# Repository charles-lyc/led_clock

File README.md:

# led_clock
led clock, matrix dot, esp32, temp/humidity/weather online and offline.

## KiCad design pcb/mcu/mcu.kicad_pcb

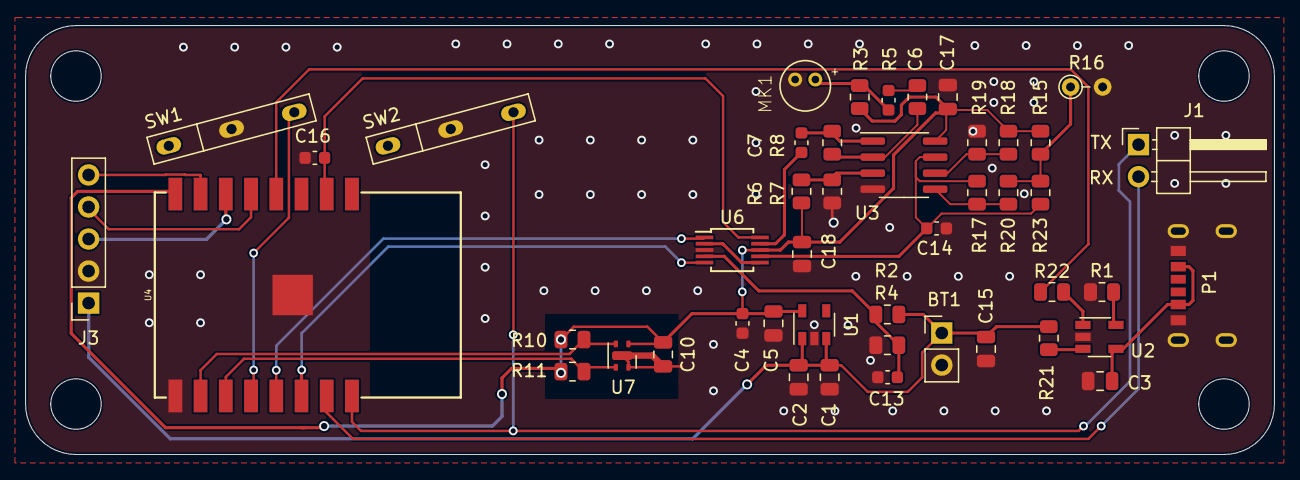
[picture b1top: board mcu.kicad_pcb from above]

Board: 2 copper layers, 99.0 x 34.0 mm, 46 parts (0 on the bottom side), 31 nets.

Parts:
BT1: Battery_Cell; PinHeader_1x02_P2.54mm_Vertical
C1, C5: 100uF; C_0805_2012Metric
C2: 0.1uF; C_0805_2012Metric
C3: 1uF; C_0805_2012Metric
C4: 0.1uF; C_0603_1608Metric
C6, C7, C14, C16: C; C_0603_1608Metric
C10: 100nF; C_0805_2012Metric
C13: 10nF; C_0603_1608Metric
C15: 200uF; C_0805_2012Metric
C17, C18: C; C_0805_2012Metric
J1: Conn_01x02_Male; PinHeader_1x02_P2.54mm_Horizontal
J3: Conn_01x05_Female; PinSocket_1x05_P2.54mm_Vertical
MK1: Microphone_Condenser; MIC_CMC_4.5x2.2mm
P1: USB_C_6PIN_POWER
R1: 2k; R_0805_2012Metric
R2: 20k; R_0805_2012Metric
R3, R5, R6, R7, R8, R15, R17, R18, R19, R20: R; R_0805_2012Metric
R4, R22: 10k; R_0805_2012Metric
R10, R11: 4.7k; R_0805_2012Metric
R16: R_PHOTO; R_Axial_DIN0204_L3.6mm_D1.6mm_P2.54mm_Vertical
R21: 0; R_0805_2012Metric
R23: 100; R_0805_2012Metric
SW1: SW_BOOT; SW_Push_Mouse_Click
SW2: SW_Push_SPDT; SW_Push_Mouse_Click
U1: SPX3819M5-L-3-3; SOT-23-5
U2: LTC4054ES5-4.2; TSOT-23-5
U3: LM358; SOIC-8_3.9x4.9mm_P1.27mm
U4: ESP-12S
U6: SGM3002_XMS; MSOP-10_3x3mm_P0.5mm
U7: SHTC3; Sensirion_DFN-4-1EP_2x2mm_P1mm_EP0.7x1.6mm

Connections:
+3V3: C4.1, C5.1, C10.1, C17.1, C18.1, R3.1, R6.1, R10.1, R11.1, R15.1, R18.1, U1.5, U3.8, U4.8, U6.8, U7.1
+5V: C3.1, P1.A9, P1.B9, U2.4
+BATT: BT1.1, C1.1, C2.1, C15.1, J3.1, R2.2, R21.1, U1.1, U1.3
/ADC_BATT: C13.1, R2.1, R4.1, U6.4
/ADC_CTRL_IN1: U4.13, U6.1
/ADC_CTRL_IN2: U4.14, U6.5
/ADC_IN: C16.1, U4.2, U6.10
/ADC_LUX: C14.1, R20.1, R23.1, U3.7, U6.7
/ADC_MIC: C7.1, U6.9
/CHARG: R22.1, U4.4
/COM2: U6.2, U6.6
/I2C_SCL: R10.2, U4.10, U7.2
/I2C_SDA: R11.2, U4.11, U7.3
/RXD: J1.2, U4.15
/SPI_CLK: J3.4, U4.5
/SPI_CS: J3.3, U4.6
/SPI_MOSI: J3.5, U4.7
/TXD: J1.1, SW2.2, U4.16
GND: BT1.2, C1.2, C2.2, C3.2, C4.2, C5.2, C10.2, C13.2, C14.2, C15.2, C16.2, C17.2, C18.2, J3.2, MK1.1, P1.A12, P1.B12, P1.S1, R1.2, R4.2, R7.2, R16.2, R19.2, SW1.3, SW2.3, U1.2, U2.2, U3.4, U4.9, U4.P$1, U6.3, U7.4, U7.5
unnamed: C6.1, R5.2
unnamed: C6.2, MK1.2, R3.2
unnamed: C7.2, R8.1, U3.1
unnamed: R1.1, U2.5
unnamed: R5.1, R8.2, U3.2
unnamed: R6.2, R7.1, U3.3
unnamed: R15.2, R16.1, R17.2, R23.2
unnamed: R17.1, R20.2, U3.5
unnamed: R18.2, R19.1, U3.6
unnamed: R21.2, U2.3
unnamed: R22.2, U2.1
unnamed: SW1.2, U4.12

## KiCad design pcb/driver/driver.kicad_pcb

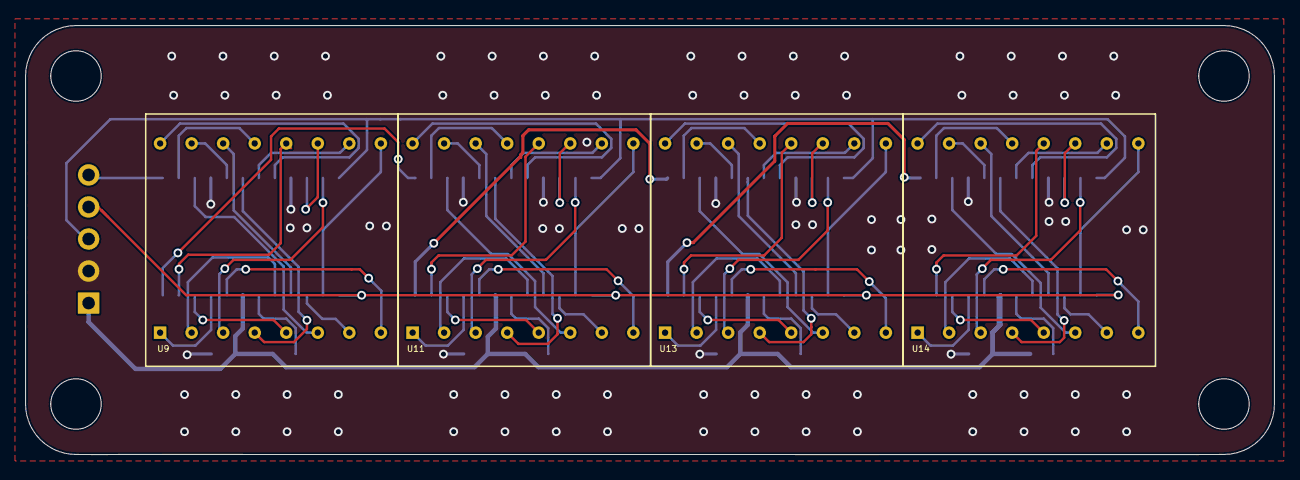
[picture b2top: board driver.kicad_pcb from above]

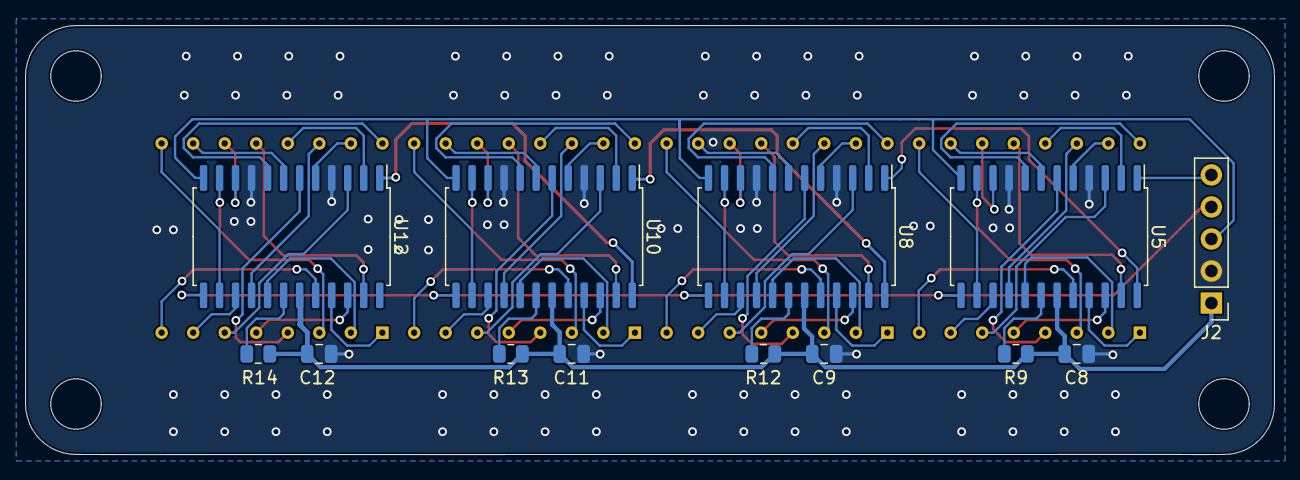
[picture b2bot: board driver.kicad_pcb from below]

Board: 2 copper layers, 99.0 x 34.0 mm, 17 parts (13 on the bottom side), 76 nets.

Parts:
C8, C9, C11, C12: 10uF; C_0805_2012Metric
J2: Conn_01x05_Male; PinHeader_1x05_P2.54mm_Vertical
R9, R12, R13, R14: 10k; R_0805_2012Metric
U5, U8, U10, U12: MAX7219; SOIC-24W_7.5x15.4mm_P1.27mm
U9, U11, U13, U14: LED_MATRIX; LED_DOT_MATRIX_8x8

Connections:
+BATT: C8.1, C9.1, C11.1, C12.1, J2.1, R9.1, R12.1, R13.1, R14.1, U5.19, U8.19, U10.19, U12.19
/SPI_CLK: J2.4, U5.13, U8.13, U10.13, U12.13
/SPI_CS: J2.3, U5.12, U8.12, U10.12, U12.12
/SPI_MOSI: J2.5, U5.1
GND: C8.2, C9.2, C11.2, C12.2, J2.2, U5.4, U5.9, U8.4, U8.9, U10.4, U10.9, U12.4, U12.9
unnamed: R9.2, U5.18
unnamed: R12.2, U8.18
unnamed: R13.2, U10.18
unnamed: R14.2, U12.18
unnamed: U5.2, U9.13
unnamed: U5.3, U9.6
unnamed: U5.5, U9.15
unnamed: U5.6, U9.4
unnamed: U5.7, U9.10
unnamed: U5.8, U9.16
unnamed: U5.10, U9.11
unnamed: U5.11, U9.3
unnamed: U5.14, U9.9
unnamed: U5.15, U9.7
unnamed: U5.16, U9.14
unnamed: U5.17, U9.2
unnamed: U5.20, U9.8
unnamed: U5.21, U9.1
unnamed: U5.22, U9.5
unnamed: U5.23, U9.12
unnamed: U5.24, U8.1
unnamed: U8.24, U10.1
unnamed: U10.2, U13.13
unnamed: U10.3, U13.6
unnamed: U10.5, U13.15
unnamed: U10.6, U13.4
unnamed: U10.7, U13.10
unnamed: U10.8, U13.16
unnamed: U10.10, U13.11
unnamed: U10.11, U13.3
unnamed: U10.14, U13.9
unnamed: U10.15, U13.7
unnamed: U10.16, U13.14
unnamed: U10.17, U13.2
unnamed: U10.20, U13.8
unnamed: U10.21, U13.1
unnamed: U10.22, U13.5
unnamed: U10.23, U13.12
unnamed: U10.24, U12.1
unnamed: U8.21, U11.1
unnamed: U8.17, U11.2
unnamed: U8.11, U11.3
unnamed: U8.6, U11.4
unnamed: U8.22, U11.5
unnamed: U8.3, U11.6
unnamed: U8.15, U11.7
unnamed: U8.20, U11.8
unnamed: U8.14, U11.9
unnamed: U8.7, U11.10
unnamed: U8.10, U11.11
unnamed: U8.23, U11.12
unnamed: U8.2, U11.13
unnamed: U8.16, U11.14
unnamed: U8.5, U11.15
unnamed: U8.8, U11.16
unnamed: U12.2, U14.13
unnamed: U12.3, U14.6
unnamed: U12.5, U14.15
unnamed: U12.6, U14.4
unnamed: U12.7, U14.10
unnamed: U12.8, U14.16
unnamed: U12.10, U14.11
unnamed: U12.11, U14.3
unnamed: U12.14, U14.9
unnamed: U12.15, U14.7
unnamed: U12.16, U14.14
unnamed: U12.17, U14.2
unnamed: U12.20, U14.8
unnamed: U12.21, U14.1
unnamed: U12.22, U14.5
unnamed: U12.23, U14.12

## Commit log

2021-03-20 完成v1.0的PCB；
2021-03-21 PCB调整 3D装配图
2021-03-22 调整目录结构；
